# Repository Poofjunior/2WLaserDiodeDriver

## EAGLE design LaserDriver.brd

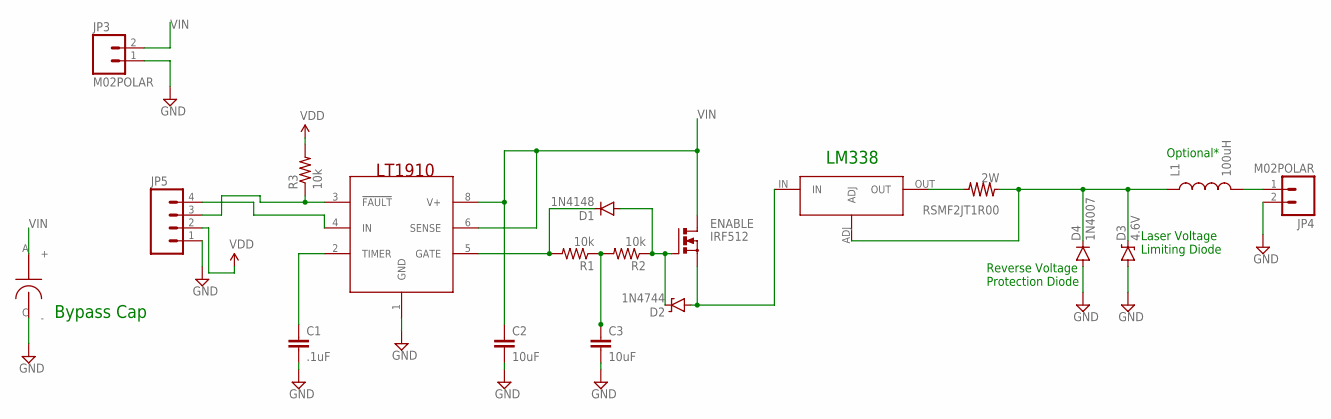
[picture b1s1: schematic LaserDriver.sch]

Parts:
BYPASS_CAP: CAP_22UF_1411; 1411
C1: .1uF; 1206
C2, C3: 10uF; 1206
D1: 1N4148; DIODE-1N4148
D2: 1N4744; DIODE-ZENER
D3: 4.6V; DIODE-ZENER
D4: 1N4007; DIODE-1N4001-KIT
ENABLE: IRF512; TO220BV
JP3, JP4: M02POLAR; MOLEX-1X2
JP5: M04SMD; 1X04-SMD
L1: 100uH; AXIAL-0.6
R1, R2, R3: 10k; 1206
RSMF2JT1R00: 2W; 2512
U$1: LT1910; SO08
U$2: LM138; TO220-IGO

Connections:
GND: BYPASS_CAP.C (-), C1.2, C2.2, C3.2, D3.P$2 (A), D4.A, JP3.1, JP4.2, JP5.1, U$1.1 (GND)
unnamed: JP4.1, L1.P$2 (2)
unnamed: JP5.3, R3.1, U$1.3 (!FAULT!)
unnamed: C1.1, U$1.2 (TIMER)
unnamed: D2.P$2 (A), ENABLE.S, U$2.IN
unnamed: C3.1, R1.1, R2.2
unnamed: D1.A, D2.P$1 (C), ENABLE.G, R2.1
unnamed: RSMF2JT1R00.P$2, U$2.OUT
unnamed: JP5.4, U$1.4 (IN)
unnamed: D1.C, R1.2, U$1.5 (GATE)
unnamed: D3.P$1 (C), D4.C, L1.P$1 (1), RSMF2JT1R00.P$1, U$2.ADJ
VDD: JP5.2, R3.2
VIN: BYPASS_CAP.A (+), C2.1, ENABLE.D, JP3.2, U$1.6 (SENSE), U$1.8 (V+)

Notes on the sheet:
Bypass Cap
LM338
Reverse Voltage Protection Diode
Laser Voltage Limiting Diode
Optional*

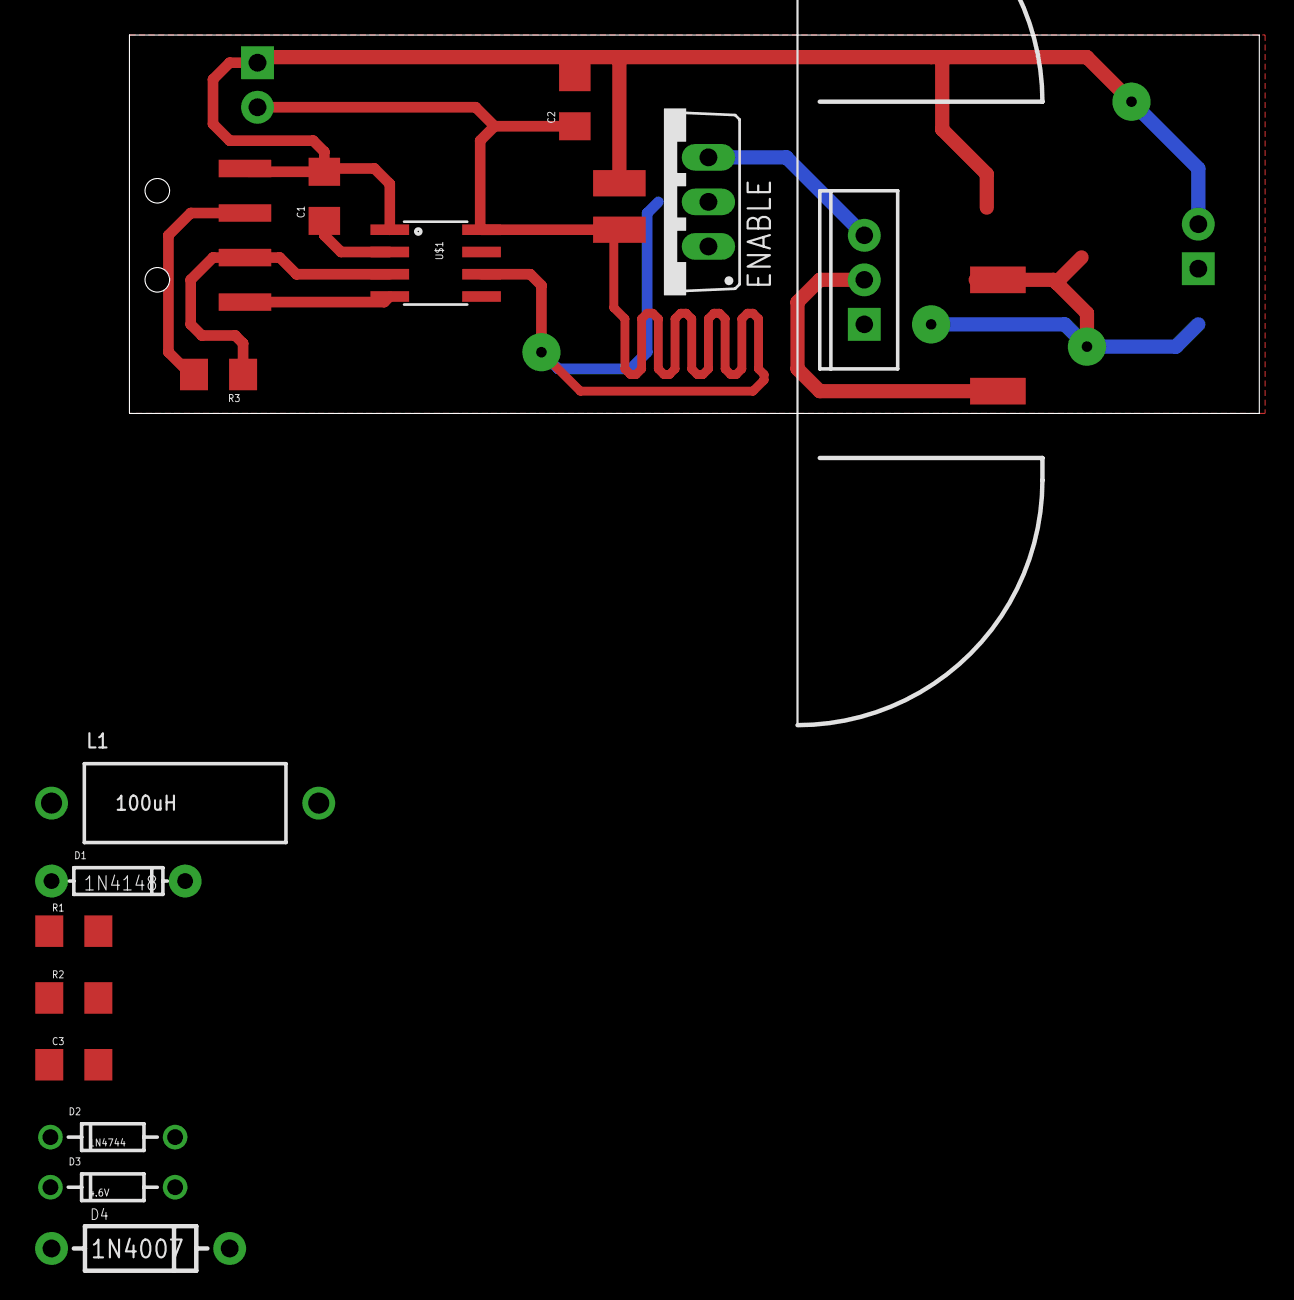
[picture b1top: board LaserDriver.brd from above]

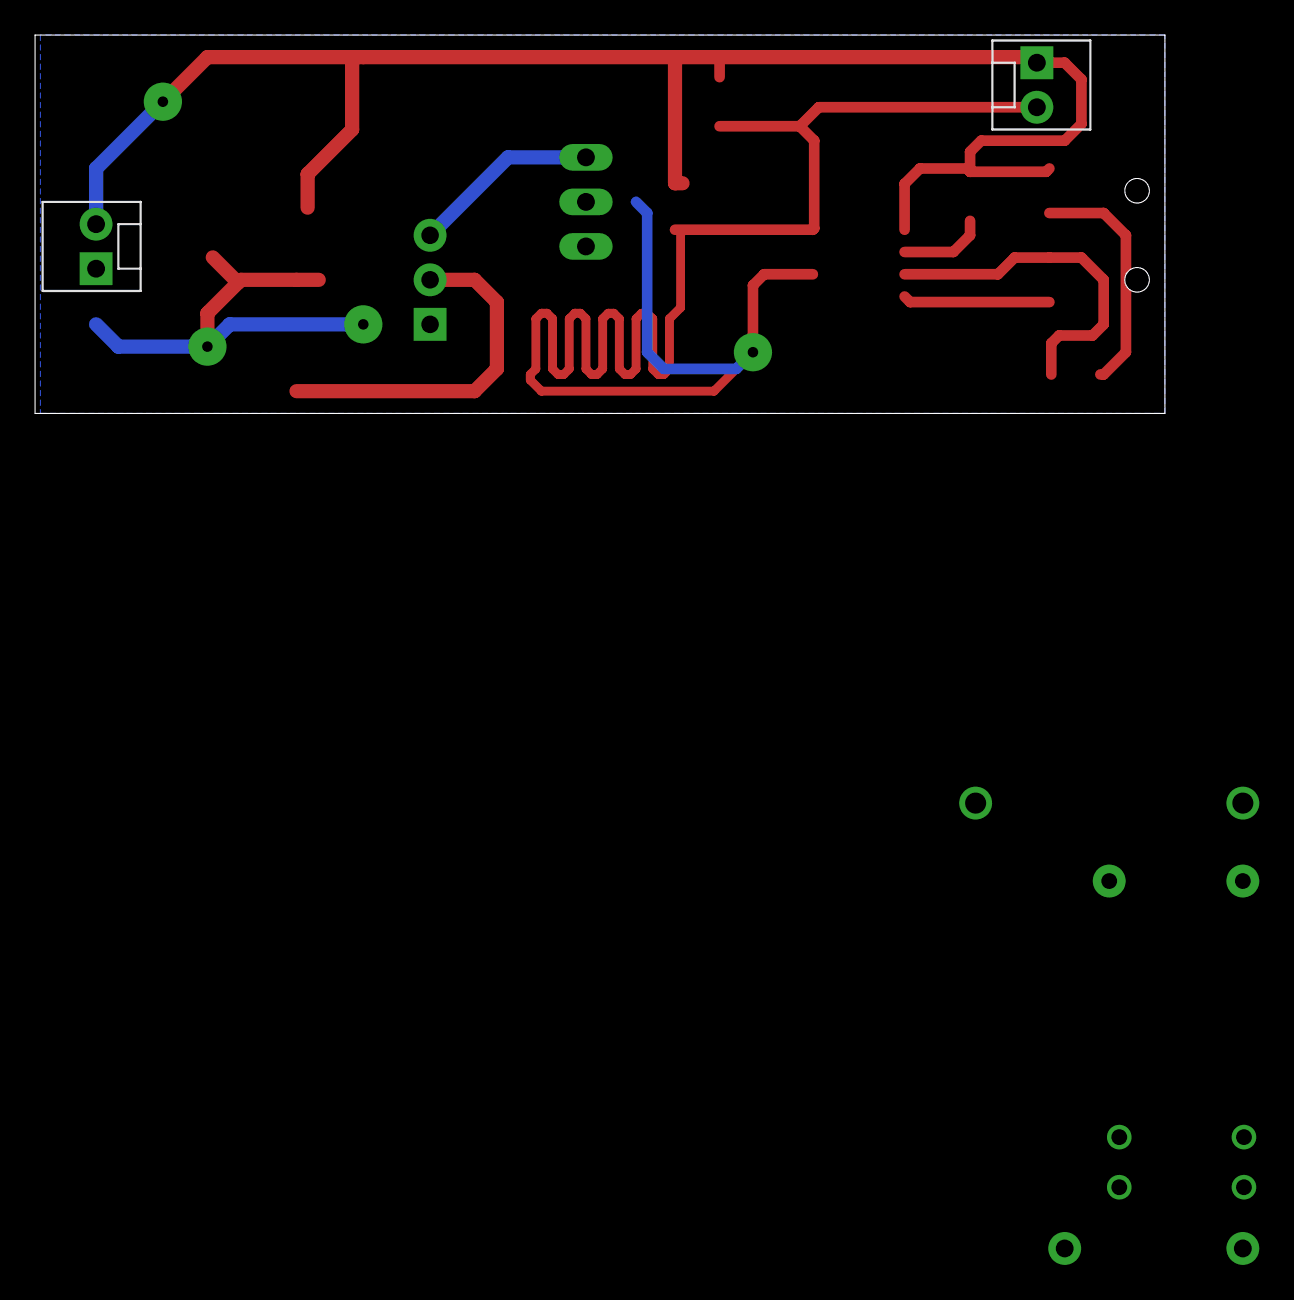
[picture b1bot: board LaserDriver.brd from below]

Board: 2 copper layers, 64.4 x 21.6 mm, 19 parts (2 on the bottom side), 13 nets.

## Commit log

2014-01-12 iniial commit
2014-09-07 revised for capacitive loads

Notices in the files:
parts and their libraries:
SparkFun-Capacitors: Licensing: CC v3.0 Share-Alike You are welcome to use this library for commercial purposes.
SparkFun-DiscreteSemi: Licensing: Creative Commons ShareAlike 4.0 International - https://creativecommons.org/licenses/by-sa/4.0
